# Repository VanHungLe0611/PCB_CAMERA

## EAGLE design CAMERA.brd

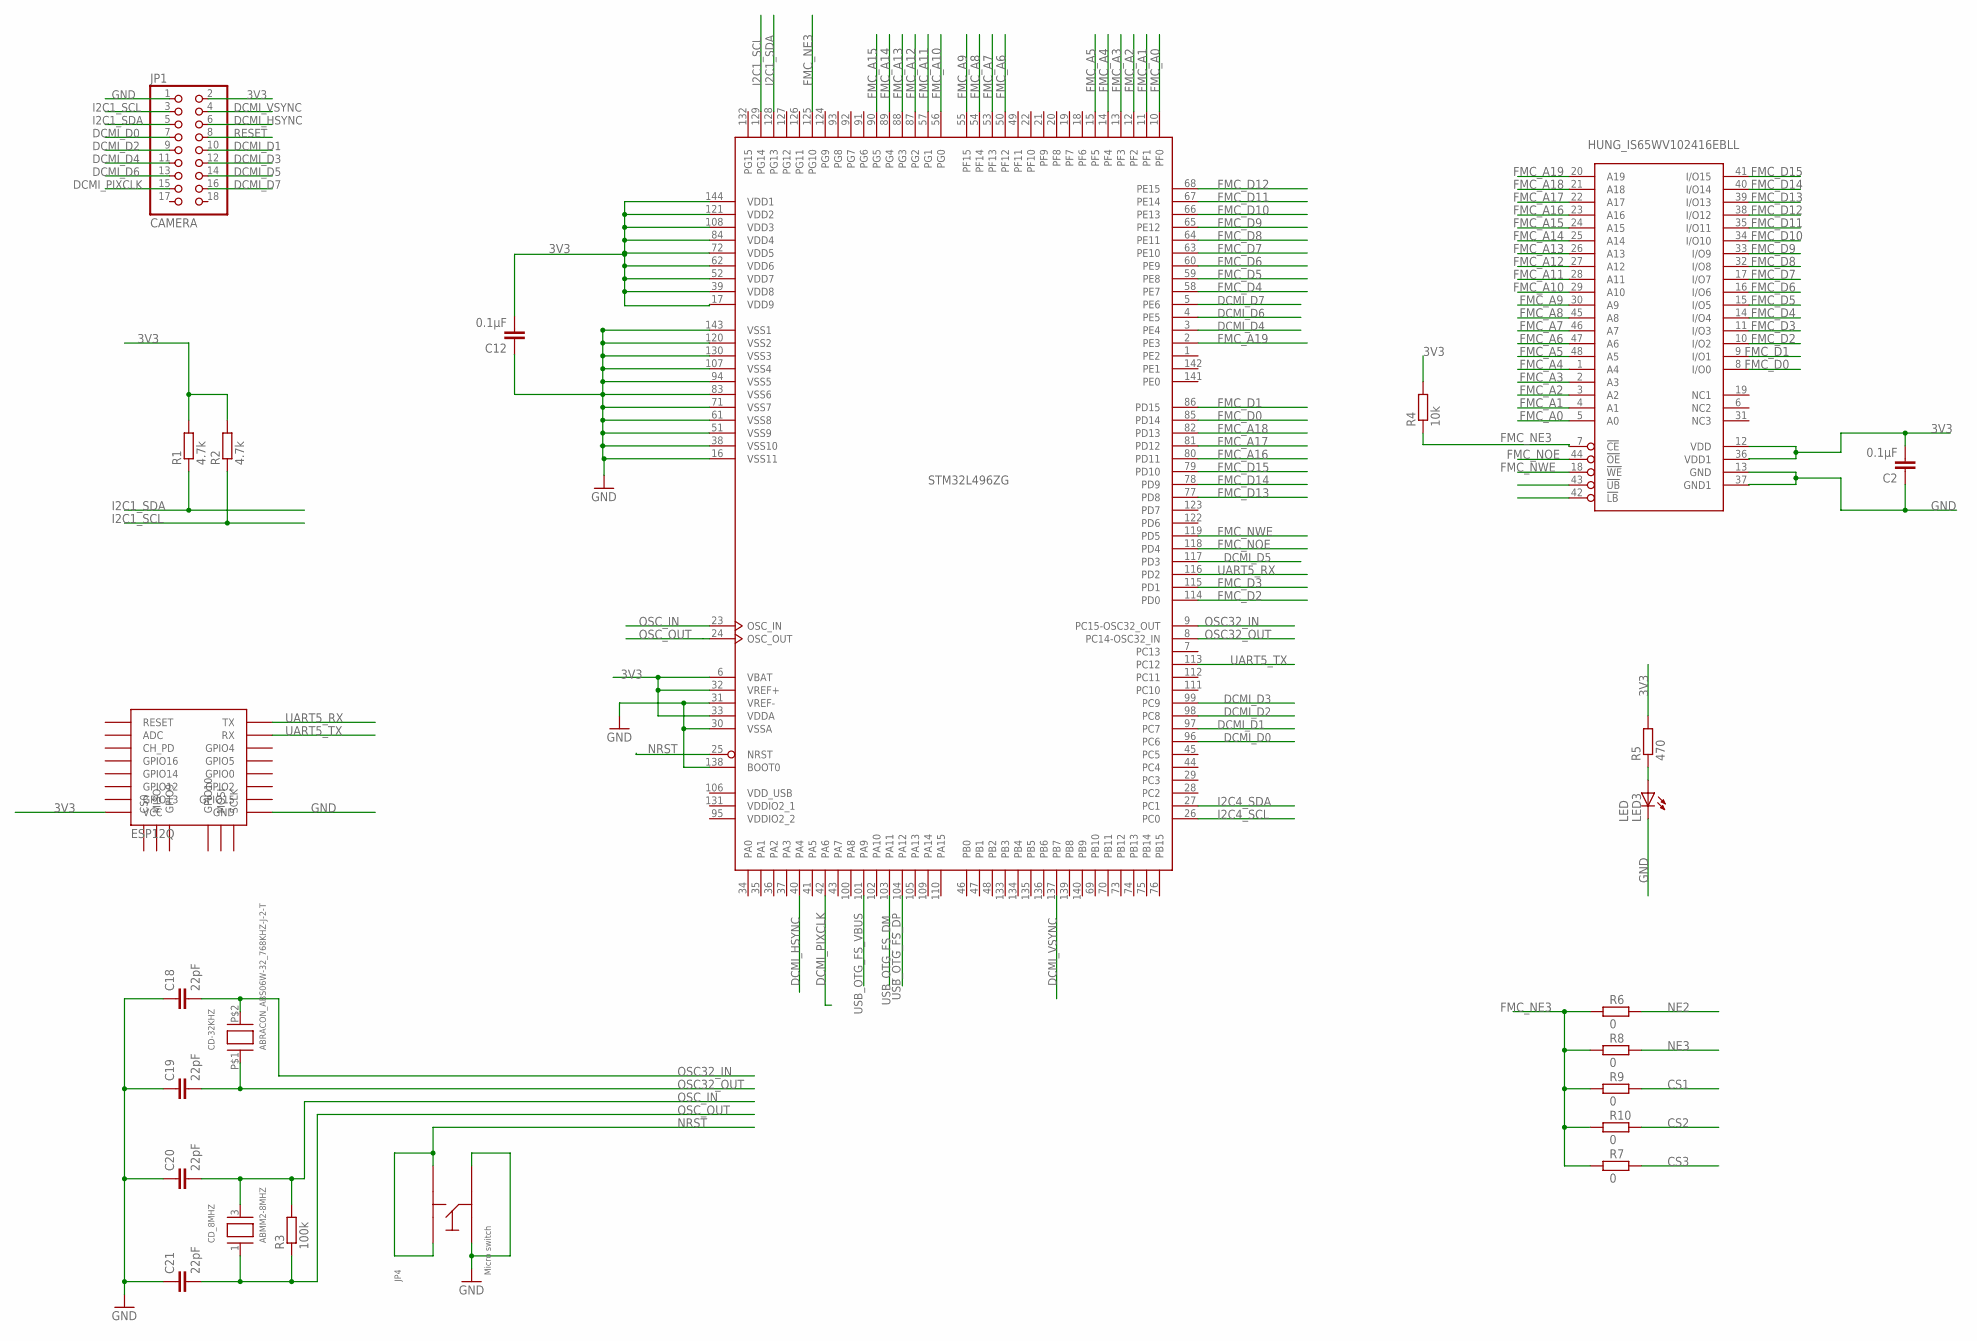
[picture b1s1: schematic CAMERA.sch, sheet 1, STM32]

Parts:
C2, C12: 0.1µF; C0402K
C18, C19, C20, C21: 22pF; C0402K
CD-32KHZ: ABRACON_ABS06W-32_768KHZ-J-2-T; 2MM_X_1_2MM
CD_8MHZ: ABMM2-8MHZ; CRYSTAL_ABRACON_6MM_3.6MM
JP1: CAMERA; 2X09
JP4: MICRO_SWITCH_6MM; SKQGADE010
LED3: LED; 0603_AK
R1, R2: 4.7k; C0402K
R3: 100k; C0402K
R4: 10k; C0402K
R5: 470; R0402
R6, R7, R8, R9, R10: 0; R0402
STM32L496ZG: STM32L496ZGT; LQFP144
U$1: HUNG_IS65WV102416EBLL; TSOP-I-48-12X40MM
U$2: ESP12Q

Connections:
3V3: C2.2, C12.2, JP1.2, R1.2, R2.2, R4.2, R5.2, STM32L496ZG.6 (VBAT), STM32L496ZG.17 (VDD9), STM32L496ZG.32 (VREF+), STM32L496ZG.33 (VDDA), STM32L496ZG.39 (VDD8), STM32L496ZG.52 (VDD7), STM32L496ZG.62 (VDD6), STM32L496ZG.72 (VDD5), STM32L496ZG.84 (VDD4), STM32L496ZG.108 (VDD3), STM32L496ZG.121 (VDD2), STM32L496ZG.144 (VDD1), U$1.12 (VDD), U$1.36 (VDD1), U$2.VCC; also elsewhere on the board
CS1: R9.2
CS2: R10.2
CS3: R7.2
DCMI_D0: JP1.7, STM32L496ZG.96 (PC6)
DCMI_D1: JP1.10, STM32L496ZG.97 (PC7)
DCMI_D2: JP1.9, STM32L496ZG.98 (PC8)
DCMI_D3: JP1.12, STM32L496ZG.99 (PC9)
DCMI_D4: JP1.11, STM32L496ZG.3 (PE4)
DCMI_D5: JP1.14, STM32L496ZG.117 (PD3)
DCMI_D6: JP1.13, STM32L496ZG.4 (PE5)
DCMI_D7: JP1.16, STM32L496ZG.5 (PE6)
DCMI_HSYNC: JP1.6, STM32L496ZG.40 (PA4)
DCMI_PIXCLK: JP1.15, STM32L496ZG.42 (PA6)
DCMI_VSYNC: JP1.4, STM32L496ZG.137 (PB7)
FMC_A0: STM32L496ZG.10 (PF0), U$1.5 (A0)
FMC_A1: STM32L496ZG.11 (PF1), U$1.4 (A1)
FMC_A2: STM32L496ZG.12 (PF2), U$1.3 (A2)
FMC_A3: STM32L496ZG.13 (PF3), U$1.2 (A3)
FMC_A4: STM32L496ZG.14 (PF4), U$1.1 (A4)
FMC_A5: STM32L496ZG.15 (PF5), U$1.48 (A5)
FMC_A6: STM32L496ZG.50 (PF12), U$1.47 (A6)
FMC_A7: STM32L496ZG.53 (PF13), U$1.46 (A7)
FMC_A8: STM32L496ZG.54 (PF14), U$1.45 (A8)
FMC_A9: STM32L496ZG.55 (PF15), U$1.30 (A9)
FMC_A10: STM32L496ZG.56 (PG0), U$1.29 (A10)
FMC_A11: STM32L496ZG.57 (PG1), U$1.28 (A11)
FMC_A12: STM32L496ZG.87 (PG2), U$1.27 (A12)
FMC_A13: STM32L496ZG.88 (PG3), U$1.26 (A13)
FMC_A14: STM32L496ZG.89 (PG4), U$1.25 (A14)
FMC_A15: STM32L496ZG.90 (PG5), U$1.24 (A15)
FMC_A16: STM32L496ZG.80 (PD11), U$1.23 (A16)
FMC_A17: STM32L496ZG.81 (PD12), U$1.22 (A17)
FMC_A18: STM32L496ZG.82 (PD13), U$1.21 (A18)
FMC_A19: STM32L496ZG.2 (PE3), U$1.20 (A19)
FMC_D0: STM32L496ZG.85 (PD14), U$1.8 (I/O0)
FMC_D1: STM32L496ZG.86 (PD15), U$1.9 (I/O1)
FMC_D2: STM32L496ZG.114 (PD0), U$1.10 (I/O2)
FMC_D3: STM32L496ZG.115 (PD1), U$1.11 (I/O3)
FMC_D4: STM32L496ZG.58 (PE7), U$1.14 (I/O4)
FMC_D5: STM32L496ZG.59 (PE8), U$1.15 (I/O5)
FMC_D6: STM32L496ZG.60 (PE9), U$1.16 (I/O6)
FMC_D7: STM32L496ZG.63 (PE10), U$1.17 (I/O7)
FMC_D8: STM32L496ZG.64 (PE11), U$1.32 (I/O8)
FMC_D9: STM32L496ZG.65 (PE12), U$1.33 (I/O9)
FMC_D10: STM32L496ZG.66 (PE13), U$1.34 (I/O10)
FMC_D11: STM32L496ZG.67 (PE14), U$1.35 (I/O11)
FMC_D12: STM32L496ZG.68 (PE15), U$1.38 (I/O12)
FMC_D13: STM32L496ZG.77 (PD8), U$1.39 (I/O13)
FMC_D14: STM32L496ZG.78 (PD9), U$1.40 (I/O14)
FMC_D15: STM32L496ZG.79 (PD10), U$1.41 (I/O15)
FMC_NBL0: U$1.42 (!LB)
FMC_NBL1: U$1.43 (!UB)
FMC_NE3: R4.1, R6.1, R7.1, R8.1, R9.1, R10.1, STM32L496ZG.125 (PG10), U$1.7 (!CE)
FMC_NOE: STM32L496ZG.118 (PD4), U$1.44 (!OE)
FMC_NWE: STM32L496ZG.119 (PD5), U$1.18 (!WE)
GND: C2.1, C12.1, C18.1, C19.1, C20.1, C21.1, JP1.1, JP4.P$3, JP4.P$4, LED3.K (C), STM32L496ZG.16 (VSS11), STM32L496ZG.30 (VSSA), STM32L496ZG.31 (VREF-), STM32L496ZG.38 (VSS10), STM32L496ZG.51 (VSS9), STM32L496ZG.61 (VSS8), STM32L496ZG.71 (VSS7), STM32L496ZG.83 (VSS6), STM32L496ZG.94 (VSS5), STM32L496ZG.107 (VSS4), STM32L496ZG.120 (VSS2), STM32L496ZG.130 (VSS3), STM32L496ZG.138 (BOOT0), STM32L496ZG.143 (VSS1), U$1.13 (GND), U$1.37 (GND1), U$2.GND; also elsewhere on the board
I2C1_SCL: JP1.3, R2.1, STM32L496ZG.129 (PG14)
I2C1_SDA: JP1.5, R1.1, STM32L496ZG.128 (PG13)
I2C4_SCL: STM32L496ZG.26 (PC0); also elsewhere on the board
I2C4_SDA: STM32L496ZG.27 (PC1); also elsewhere on the board
unnamed: LED3.A, R5.1
NE2: R6.2
NE3: R8.2
NRST: JP4.P$1, JP4.P$2, STM32L496ZG.25 (NRST)
OSC32_IN: C18.2, CD-32KHZ.P$2 (C1), STM32L496ZG.9 (PC15-OSC32_OUT)
OSC32_OUT: C19.2, CD-32KHZ.P$1 (C0), STM32L496ZG.8 (PC14-OSC32_IN)
OSC_IN: C20.2, CD_8MHZ.3 (C1), R3.2, STM32L496ZG.23 (OSC_IN)
OSC_OUT: C21.2, CD_8MHZ.1 (C0), R3.1, STM32L496ZG.24 (OSC_OUT)
RESET: JP1.8
UART5_RX: STM32L496ZG.116 (PD2), U$2.TX
UART5_TX: STM32L496ZG.113 (PC12), U$2.RX
USB_OTG_FS_DM: STM32L496ZG.103 (PA11); also elsewhere on the board
USB_OTG_FS_DP: STM32L496ZG.104 (PA12); also elsewhere on the board
USB_OTG_FS_VBUS: STM32L496ZG.101 (PA9); also elsewhere on the board

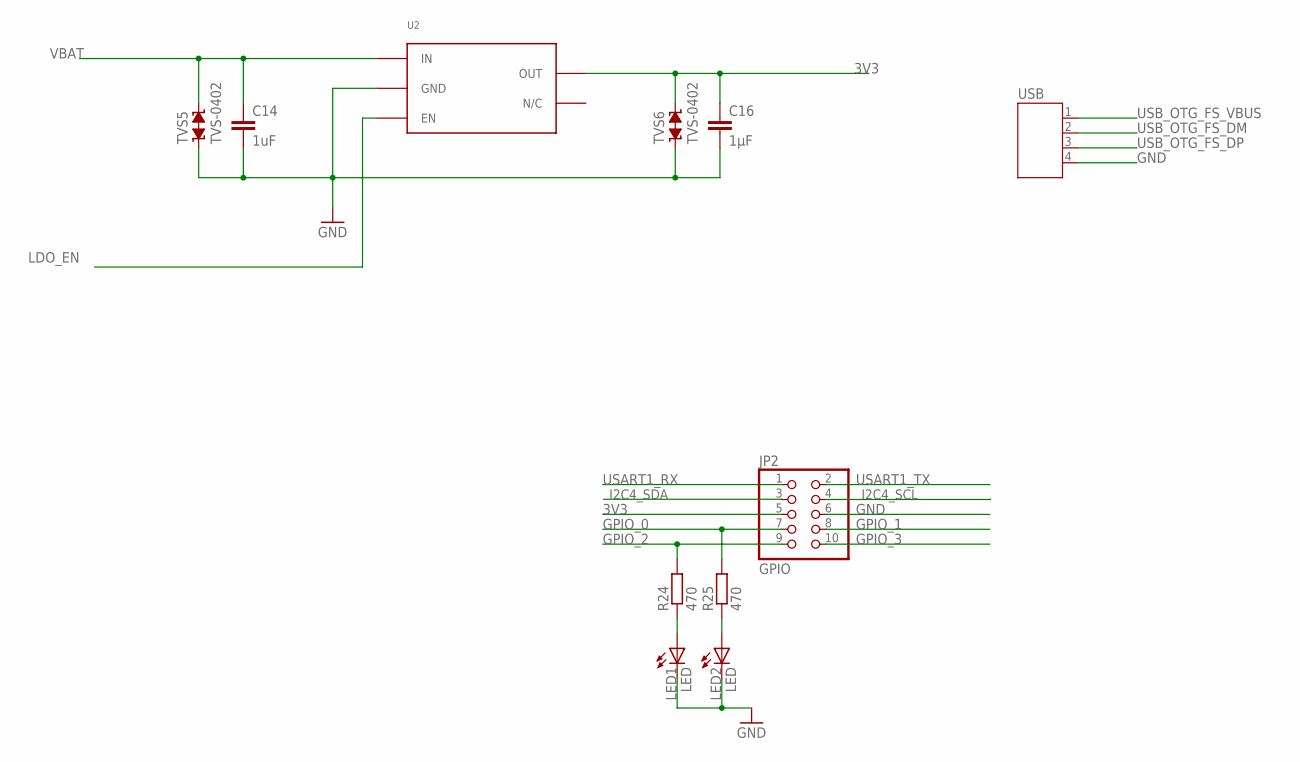
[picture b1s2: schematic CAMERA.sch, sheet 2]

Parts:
C14: 1uF; C0402K
C16: 1µF; C0402K
JP2: GPIO; 2X05
LED1, LED2: LED; 0603_AK
R24, R25: 470; R0402
TVS5, TVS6: TVS-0402; TVS0402
U2: NCP702; SOT563
USB: JST-PH4

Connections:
3V3: C16.1, JP2.5, TVS6.2, U2.P$5 (OUT); also elsewhere on the board
GND: C14.2, C16.2, JP2.6, LED1.K (C), LED2.K (C), TVS5.1, TVS6.1, U2.P$2 (GND), USB.4; also elsewhere on the board
GPIO_0: JP2.7, R25.2
GPIO_1: JP2.8
GPIO_2: JP2.9, R24.2
GPIO_3: JP2.10
I2C4_SCL: JP2.4; also elsewhere on the board
I2C4_SDA: JP2.3; also elsewhere on the board
LDO_EN: U2.P$3 (EN)
unnamed: LED1.A, R24.1
unnamed: LED2.A, R25.1
USART1_RX: JP2.1
USART1_TX: JP2.2
USB_OTG_FS_DM: USB.2; also elsewhere on the board
USB_OTG_FS_DP: USB.3; also elsewhere on the board
USB_OTG_FS_VBUS: USB.1; also elsewhere on the board
VBAT: C14.1, TVS5.2, U2.P$1 (IN)

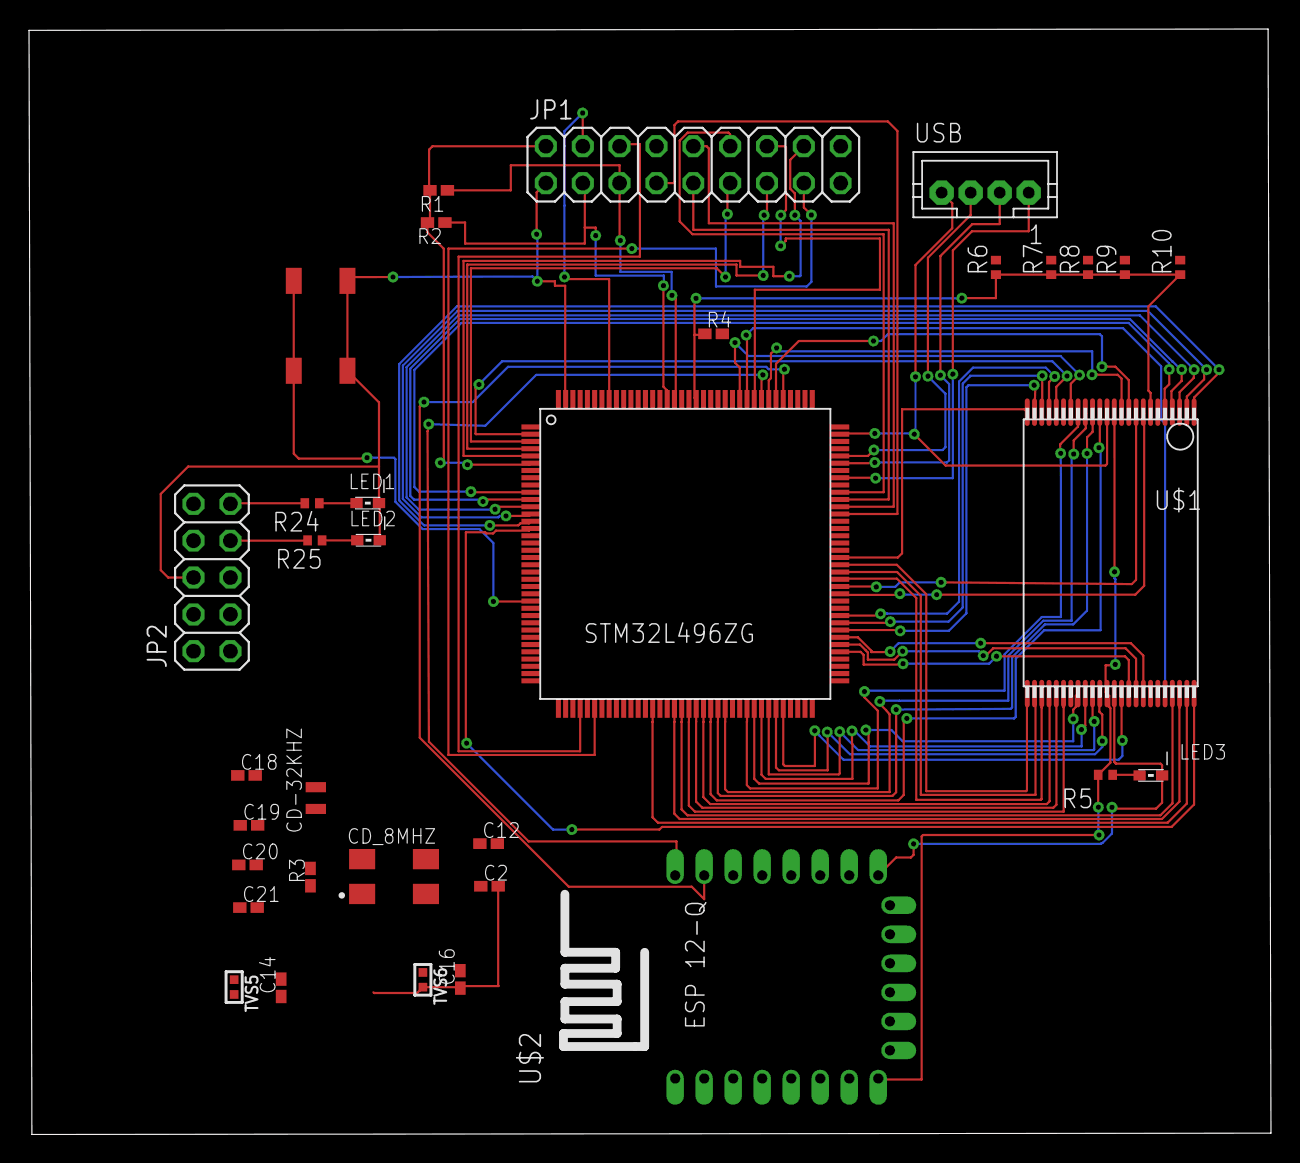
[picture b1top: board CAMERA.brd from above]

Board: 2 copper layers, 85.6 x 76.2 mm, 35 parts (1 on the bottom side), 72 nets.

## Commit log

2019-09-03 pcb with eagle

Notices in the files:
parts and their libraries:
supressor: Copyright (C) 2009, Bob Starr
